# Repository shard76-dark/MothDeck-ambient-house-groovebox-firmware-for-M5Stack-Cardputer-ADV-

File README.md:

# MothDeck

MothDeck is ambient-house groovebox firmware for the [M5Stack Cardputer ADV](https://docs.m5stack.com/en/core/Cardputer-Adv) (Stamp-S3A, ESP32-S3): drums, a per-track FX insert, a four-track mixer, SD kits and loops, and BLE MIDI. It is a sibling of [MothOS](https://github.com/MothSynths): same song file, same BLE MIDI map, same voice and effect model, redrawn for the ADV's 240×135 colour screen and 56-key keyboard.

## Download the binary

**Use earphones or headphones.** Plug them into the 3.5 mm jack on the side of the Cardputer ADV. This firmware does not play through the internal speaker. The jack is how you hear the drums, the kits, and the loops. Unplugging the earphones does not switch the sound to the speaker.

**Latest Cardputer ADV image (flash this):** [`releases/mothdeck-cardputer-adv.bin`](releases/mothdeck-cardputer-adv.bin)

- Version 1.2.12
- SHA-256: `9b98e52296c0634d2577b3fa6f98c0125cec331b60e1f9f07e440d255c90aa24`
- Size: 1,235,872 bytes (app image, magic `E9`)
- 1.2.12 follows an external clock from the incoming ticks, keeps several MIDI channels sounding at once, and answers `status` with DTR and RTS low. Details are in [What 1.2.12 includes](#what-1212-includes). The air name is `Mothdeck`. Patterns are 1–8 bars and Play opens on a piano roll. Notes are in [`releases/CHANGELOG.md`](releases/CHANGELOG.md).
- Install notes: [`releases/INSTALL.md`](releases/INSTALL.md) — copy the `.bin` to a FAT32 card, install from [Launcher](https://github.com/bmorcelli/Launcher)
- Optional SD kits/loops: [`releases/mothdeck-sd-pack.zip`](releases/mothdeck-sd-pack.zip) · checksums: [`releases/SHA256SUMS`](releases/SHA256SUMS)

The public source and releases live in this repository. Flash the application image with [releases/INSTALL.md](releases/INSTALL.md). The same overview, with HTML meta tags for search and link previews, is [docs/index.html](docs/index.html).

## What 1.2.12 includes

1.2.12 is the Cardputer image to flash. It includes the 1.2.2 through 1.2.11 behavior. This image has not been tried on a Cardputer. Use earphones.

- **External sync.** Tempo is the incoming tick count over the timestamps. One beat follows a change. Two beats hold a steady tempo, so 80–138 land on that integer and a jump up to 180 shows within about two beats. The deck BPM is the fallback only when a gap is much longer than one tick. Copies of one tick count once. A run of sub-tick clocks does not race the playhead. Faster than 200 clamps to 200.
- **Live MIDI.** The event ring is 48 slots (was 256), the note-off tail is 16 (was 32), and clock groups are 32 (was 64). A note-on older than 40 ms is dropped. Note-offs stay. Clocks stay a counter.
- **Channels.** Channels 1, 5, 9, and 13 play track 1. Channels 2, 6, 10, and 14 play track 2. Channels 3, 7, 11, and 15 play track 3. Channels 4, 8, 12, and 16 play track 4. Channels 1–4 also select that track. Each track keeps its own four voices.
- **USB serial.** `status`, `help`, and `version` answer when the host leaves DTR and RTS low.
- **MothDiag 0.1.6.** Stats add `clock_hz`, the raw clock bytes per second. The clock line shows the musical rate and the raw rate. The image is [`releases/mothdiag-0.1.6.bin`](releases/mothdiag-0.1.6.bin).

## What 1.2.11 includes

1.2.11 is included in the 1.2.12 image. It includes the 1.2.2 through 1.2.10 behavior. This image has not been tried on a Cardputer. Use earphones.

- **Slot versions.** MothBoot 0.1.2 reads the version from the whole application image, so slot B shows the installed MothDeck version. MothBoot 0.1.2 is [`releases/mothboot-0.1.2.bin`](releases/mothboot-0.1.2.bin). Write it at `0x10000` from the ROM bootloader. A board already on 0.1.1 can keep that launcher for uploads.
- **USB serial.** `status`, `help`, and `version` answer on MothDeck's CDC port. Opening the port does not reboot the board into download mode.
- **Install from an app.** `diag.py --flash` sends `launcher` when an app is running, waits for MothBoot, and then copies the image. The port number can change on that reboot.
- **External sync.** A smoothed tempo locks to 180 from a full-rate clock or a thinned one. Duplicate clocks and a sub-tick burst do not race the playhead. The deck still needs to be near the source tempo for a thinned clock.
- **MothDiag 0.1.5.** Clocks are counted in the BLE callback, so a full-rate MPC does not fill the packet queue. MIDI BPM handles the 13-bit timestamp wrap and repeated timestamps. The image is [`releases/mothdiag-0.1.5.bin`](releases/mothdiag-0.1.5.bin).

## What 1.2.10 includes

1.2.10 is included in the 1.2.11 image. It includes the 1.2.2 through 1.2.9 behavior. Use earphones.

- **MothBoot.** Sending `launcher` restarts into MothBoot on the USB-Serial-JTAG port. MothBoot 0.1.1 is [`releases/mothboot-0.1.1.bin`](releases/mothboot-0.1.1.bin). A board still running MothBoot 0.1.0 needs a later factory image from the ROM bootloader before `--flash` can run at full speed.
- **Uploads.** `diag.py --flash` and `--sd-put` wait for an ack after each chunk and draw a progress bar.
- **MothDiag 0.1.4.** `status`, `help`, `stats`, and command replies are always sent. The image is [`releases/mothdiag-0.1.4.bin`](releases/mothdiag-0.1.4.bin).

## What 1.2.9 includes

1.2.9 is included in the 1.2.10 image. It includes the 1.2.2 through 1.2.8 behavior. This image has not been tried on a Cardputer. Use earphones.

- **Sync.** Settings has Internal, External, and Transport. External follows MIDI start, stop, and song position. Tempo comes from the BLE timestamps: a gap that covers several ticks of the current BPM is counted as those ticks. Set the deck near the MPC's tempo, then switch to External. Transport follows start, stop, and position and keeps the BPM you set. Internal keeps the deck clock.
- **MTC.** Quarter frames can start and stop the transport. When their spacing matches the rate in the message, the playhead seeks. A half-rate stream leaves the tempo on the deck, or on the scaled clock when MIDI clocks are arriving too.
- **MothDiag 0.1.3.** The diagnostic screen shows MIDI BPM, arrival BPM, the clock rate, and the MTC rate, and it redraws only the line that changed. Published as [`releases/mothdiag-0.1.3.bin`](releases/mothdiag-0.1.3.bin).

## What 1.2.8 includes

1.2.8 is included in the 1.2.9 image. It includes the 1.2.2 through 1.2.7 behavior. This image has not been tried on a Cardputer. Use earphones.

- **Clock.** An external clock follows the master from 40 to 200 BPM, including when several clocks share one BLE timestamp. The short-interval request stays pending until the link is 15 ms or faster, and it is asked again while the link is still slow. A catch-up of more than one step moves the playhead and sounds the step it lands on.
- **Notes.** A status byte after a clock is the note, unless another status follows it. A note-on that arrives while note-offs are waiting is queued behind them. A long run of clocks does not push the notes out of the packet.
- **USB MIDI.** The USB port is a MIDI device named Mothdeck and still a serial port. USB notes and clock use the same queue as BLE. Unplugging USB releases live notes. The MIDI page shows `USB MIDI` while a host has enumerated the port, and `USB off` otherwise.

## What 1.2.7 includes

1.2.7 is included in the 1.2.8 image. It has not been tried on a Cardputer on its own. Use earphones.

- **Gate.** With Rec on, a MIDI note-off stores how long the note was held. The length is 1 to 4 steps, in the same two bits a piano-roll hold already uses. The song file does not change. Rec off still only plays.
- **Quantize.** The note lands on the step that just played. Three or more of the six clocks in that step, or halfway through an internal step, move it to the next step. A late note at the end of the pattern wraps to step 0 of that same pattern, including while song mode is moving on to the next one.

## What 1.2.6 includes

1.2.6 is included in the 1.2.8 image. It has not been tried on a Cardputer on its own. Use earphones.

- **Clock counter.** MIDI clocks are counted instead of taking a queue slot each. A burst of ticks, including a 200 BPM run, still advances the pattern, and the notes in that packet stay behind the ticks that preceded them. Start, Continue, Stop, and Song Position stay in the queue in that order. Start clears ticks that have not been applied yet, and ticks that sit before Start in the same packet are not counted. Clocks between Song Position and Continue still count.
- **Quiet connect.** The production build does not print from the connect and interval callbacks. Pairing, the advertising packet, and the 7.5–15 ms request are unchanged. The dev build still prints those lines.

## What 1.2.5 includes

1.2.5 is included in the 1.2.8 image. It has not been tried on a Cardputer on its own. Use earphones.

- **Stop and disconnect.** MIDI Stop, and a Bluetooth link that drops, release live MIDI notes. The pattern, loops, and sampler keep going. CC 120 and CC 123 do the same for the channel that sent them.
- **Note-off.** A note-off releases the matching note and channel on whichever track sounded it, and it does not change the selected track. Controllers, then note-ons, give up queue slots first. A note-off or a transport message is kept while any of those can move.
- **Continue.** Continue stays on the current step. Clocks that arrived after a Song Position still count, so the step does not slip by a tick. An external clock still reads 40–200 BPM, and a faster clock clamps at 200.
- **Status.** The Settings page no longer prints a counter line. The MIDI page counts packets, messages, clocks, and notes. Fn+D on that page opens a status view with the shed counts, how long the MIDI drain took, and the step length of the safety release. Backspace closes it. A tonal note with no note-off releases after that many steps (192 by default, about 24 seconds at 120 BPM). Held arp is not timed.

## What 1.2.4 includes

1.2.4 is included in the 1.2.8 image. It has not been tried on a Cardputer on its own. Use earphones.

- **1.2.2.** NimBLE is reserved at boot, before the loop windows. Turning BLE on starts advertising and does not allocate, so it does not fail for lack of a free block. Unload BLE skips the stack on the next boot and frees that block for a large loop library. The toast says `BLE unloads after restart`.
- **1.2.3.** Incoming MIDI notes only play while Rec is off. They are not written into the pattern. Space turns Rec on, and then they record at the playhead. MIDI Start and Continue do not arm Rec. A piano-roll key while the transport is running follows that same rule.
- **1.2.4.** An external clock counts every `0xF8` in a BLE packet, including several that share one timestamp. Six clocks advance one 16th. The BPM on screen is smoothed over a beat and tracks from 40 to 200. A track sounds up to four notes at once. A fifth replaces the oldest. Note-off, including velocity 0, releases only the matching note and channel, so a stolen or retriggered note does not cut a different voice. Notes that arrive in one packet each get a voice. When the MIDI queue is nearly full, extra clocks are dropped so a chord behind them is kept.

## LilyGO TTGO T8

A separate port of MothDeck 1.2.4 runs on a LilyGO TTGO T8 V1.8 (ESP32-WROVER, 4MB flash, 4MB PSRAM, microSD). It lives on the [`ttgo-t8` branch](https://github.com/shard76-dark/MothDeck-ambient-house-groovebox-firmware-for-M5Stack-Cardputer-ADV-/tree/ttgo-t8) and is not merged into `main`. The Cardputer image in `releases/` is a different binary. Do not flash a TTGO image onto a Cardputer, or the Cardputer image onto a T8.

The pre-release is [ttgo-t8-v1.2.4](https://github.com/shard76-dark/MothDeck-ambient-house-groovebox-firmware-for-M5Stack-Cardputer-ADV-/releases/tag/ttgo-t8-v1.2.4). Wiring, the menu tree, and both images are in [docs/TTGO-T8.md](https://github.com/shard76-dark/MothDeck-ambient-house-groovebox-firmware-for-M5Stack-Cardputer-ADV-/blob/ttgo-t8/docs/TTGO-T8.md) on that branch.

- **PSRAM.** Loop windows, samples, the pattern grid, chord notes, and the tracker sit in PSRAM, so BLE and loops stay loaded together.
- **Chords.** A step holds up to four notes. The first stays in the song file, so an older song still loads. The other three are stored in PSRAM. With Rec on, MIDI notes that land in the same step stack. The piano roll draws each one as a block in that column.
- **4×4 keypad.** A membrane keypad mounted with the connector on top, so the top-left key is key 0. The menu is the original MothSynth function-key layout, extended so every MothDeck page is reachable from the 16 keys.
- **ST7789 and audio.** The stock image drives a confirmed ST7789 240×135. `ttgo-t8` plays through a PCM5102A over I2S. `ttgo-t8-dac` uses the ESP32's internal 8-bit DAC on GPIO25. Keypad R3 is GPIO25 on the PCM image and GPIO22 on the DAC image.

These TTGO images have not been flashed, and the keys have not been pressed on hardware.

## ESP32 DevKit handheld

A second target on this branch is a small handheld on a classic ESP32-WROOM-32 board, the 30-pin DOIT ESP32 DevKit V1 (ESP32-D0WD). Build it with `pio run -e esp32devkit_handheld`. The Cardputer envs are unchanged. The LilyGO T8 port stays on `ttgo-t8`; this carrier reuses that port's PCM5102A audio path and its 4×4 menu, and it does not merge the 1.2.4 tree.

The DevKit's own AMS1117 cannot run from one Li-ion cell (dropout is about 1.1 V). The carrier feeds 3.3 V into the DevKit 3V3 pin from an AP2112K-3.3 and leaves VIN open. Turn the slide switch off while flashing so the AP2112 and the DevKit regulator are not both on the 3.3 V rail.

### Pin table

Silkscreen on clone DevKits varies. Match the labels on the board you have. GPIO0, GPIO2, GPIO12, and GPIO15 are left open (strapping). GPIO6–11 are the flash bus and are not on the header. GPIO1 and GPIO3 stay on the USB UART. GPIO34, GPIO35, GPIO36, and GPIO39 are input-only, so the column pull-ups are on the carrier.

| Function | GPIO | Notes |
| --- | --- | --- |
| I2C SDA | 21 | SSD1306 0x3C and HT16K33 0x70, 4.7 kΩ to 3.3 V |
| I2C SCL | 22 | same bus |
| I2S BCLK | 26 | PCM5102A BCK |
| I2S WS | 25 | PCM5102A LCK |
| I2S DOUT | 27 | PCM5102A DIN |
| PCM5102A SCK | GND | PLL mode, not a GPIO |
| Keypad R1–R4 | 16, 17, 18, 19 | outputs, membrane order |
| Keypad C1–C4 | 34, 35, 36, 39 | inputs, 10 kΩ to 3.3 V |
| LED step | 4 | GPIO → 470 Ω → LED → GND |
| LED beat | 5 | same, active high |
| LED play | 13 | same |
| LED record | 14 | same. GPIO14 can twitch during boot |
| Battery sense | 33 | ADC1, 100 kΩ / 100 kΩ from the cell, 100 nF to GND |

### Keypad

Mount the membrane on the left of the case, rotated 90° clockwise, so the ribbon that sat at the bottom of an upright legend now leaves to the left. Straight wiring, membrane order R1 R2 R3 R4 C1 C2 C3 C4. The printed legend is sideways after the turn:

```
*  7  4  1
0  8  5  2
#  9  6  3
D  C  B  A
```

The firmware numbers keys in reading order on the upright device. Key 0 is the top-left key. `handheldPadKey(membraneRow, membraneCol) = membraneCol * 4 + (3 - membraneRow)`. The menu is the MothSynth 4×4 layout used on the T8: F1–F4 on the top row latch, then the next key runs that function. The note rows underneath are C at the bottom left. Holding F1 for about half a second arms BPM nudge (C −1, C# +1, D −5, D# +5).

### Power

Cell: a 603450 1200 mAh LiPo with a JST-PH 2.0 plug (about 6 × 34 × 50 mm). It fits the left bay under the keypad. An 18650 is cheaper per mAh and too thick for this case.

Charger: a TP4056 USB-C module that already includes the DW01 protection cell. The slide switch (SS-12D00 or similar) sits between the charger OUT+ and the AP2112 input. The AP2112K-3.3 (SOT-23-5, 600 mA) makes 3.3 V. EN is tied to VIN. 10 µF on the input, 10 µF on the output, 22 nF on BP.

Playing with BLE is budgeted at about 170 mA. Usable capacity is about 1200 × 0.85 mAh, so runtime is about six hours. Without the radio, about 110 mA and about nine hours.

### What is on the carrier

The board is 66 × 78 mm, two layers. Headers for the DevKit, the PCM5102A (jack toward the right edge), the SSD1306, the HT16K33 backpack, the keypad ribbon, and the TP4056. The four LEDs and the battery sense divider are on the board. Ground is a tracked mesh. KiCad 7's zone filler crashes in the environment this board was generated in, so there is no copper pour. Power tracks are 0.25 mm because a 0.5 mm track cannot pass between the 1.7 mm header pads.

The case is 154 × 96 × 22 mm. The membrane is on the left, the carrier on the right, the headphone socket on the right wall, USB-C and the DevKit USB socket on the bottom wall, and the 603450 in a tray under the keypad. Source is `hardware/mothdeck-handheld/case/mothdeck-handheld-case.scad`.

### BOM, approximate AUD

| Qty | Part | AUD |
| --- | --- | --- |
| 1 | ESP32 DevKit V1 30-pin | 9 |
| 1 | PCM5102A purple DAC board | 6 |
| 1 | SSD1306 128×64 I2C OLED | 6 |
| 1 | HT16K33 4-digit backpack | 8 |
| 1 | 4×4 membrane keypad | 3 |
| 1 | TP4056 USB-C module with protection | 3 |
| 1 | 603450 1200 mAh LiPo, JST-PH | 12 |
| 1 | AP2112K-3.3 | 0.50 |
| 1 | SS-12D00 slide switch | 0.80 |
| 4 | 3 mm LEDs | 0.40 |
| 1 | passives, headers, JST | 5 |
| 1 | PCB, five from JLCPCB, this board's share | 2 |
| 1 | PETG for the case | 2 |

About 58 AUD before shipping. Prices move; treat them as a shopping list, not a quote.

### Assembly

1. Confirm the DevKit silkscreen against the pin table before soldering the headers.
2. Solder the AP2112, the passives, and the LED resistors first. The LED anode is the resistor side, not the GPIO.
3. Add the headers. The PCM5102A SCK pin on the module is the one tied to ground on the carrier.
4. Flash with the slide switch off and USB plugged into the DevKit, not the charger.
5. Switch on from the battery only after 3.3 V measures about 3.3 V at the DevKit 3V3 pin.
6. The OLED and the 7-segment are wired to their headers and sit in the lid. While a pattern is running the 7-segment shows bar and beat. Stopped, it shows BPM.

### Trade-offs

- Both the 7-segment and the four LEDs fit.
- No microSD. Kits and loops that need the card are absent. The built-in drums and synths play.
- No USB MIDI. The DevKit USB port is a UART bridge. BLE MIDI is the transport. The image links with about 40 KB of DRAM left, and the BLE start check asks for a 36 KB contiguous block, so the radio can still refuse until a reboot frees enough. That is untested on hardware.
- The delay history is 2048 samples, about 46 ms, instead of the Cardputer's 8192.
- GPIO5 and GPIO14 can glitch high for a moment at boot. The beat and record LEDs may flash then.
- Ground is tracked, not poured, and the power tracks are 0.25 mm.

## Features

- Ambient house drums on the M5Stack Cardputer ADV: twelve distinct hits at the recorded pitch (kick, rim, snare, clap, hats, toms, shaker, ride, snap, crash)
- Groovebox session on the ESP32-S3: 4 tracks, patterns of 1–8 bars (16–128 steps of 16th notes)
- Per-track FX (filter, delay, reverb, bitcrush, drive, chorus, tremolo) and a mixer with volume, mute, and solo
- SD kits, plugin instruments, and loops. Loops stream from the card instead of filling RAM
- BLE MIDI peripheral (notes, clock, transport, bank, volume, pitch bend), named Mothdeck in the advertising packet, and a USB MIDI device on the same port as serial
- Built-in sounds are unsigned 8-bit mono at 22050 Hz so they fit the 8MB flash and the internal SRAM
- One-second amber moth splash, then the Play page, with a checked exit back to Launcher

This repository is the Cardputer ADV firmware. The PlatformIO target is `cardputer-adv`. `cardputer-adv-dev` is that same firmware with SD and speaker logs on USB serial. The board id in `platformio.ini` is `esp32-s3-devkitc-1` because PlatformIO has no Stamp-S3A entry; the pins in `include/BoardConfig.h` are the ADV. There is no second ADV build.

Everything it uses is on the board. There is no wiring. The headphone jack, display, keyboard, and microSD are brought up by M5Unified. The internal speaker does not play with this firmware; use earphones or headphones in the 3.5 mm jack. A card is optional. The built-in drums, sound effects, and tonal instruments are synthesized when the firmware is built. They are not recordings of anyone else's samples.

## Flash it

See [releases/INSTALL.md](releases/INSTALL.md) for the button sequence. Short version:

1. Copy `releases/mothdeck-cardputer-adv.bin` (the file that starts with `E9`) to a FAT32 card.
2. Boot [Launcher](https://github.com/bmorcelli/Launcher), press Enter on its splash, and install that file from the SD browser.
3. The next boot that follows the boot selection starts MothDeck.

`mothdeck-cardputer-adv-full.bin` is a USB flash of the whole chip. It replaces Launcher. Checksums for both images and for `mothdeck-sd-pack.zip` are in `releases/SHA256SUMS`.

Unzip `releases/mothdeck-sd-pack.zip` onto the card root when you want the extra kits, loops, and plugin instruments. You should end up with a `moth` folder at the top of the card. The built-in kit does not need the card.

## Boot

Power-on turns the backlight on, draws an amber moth on a grey panel for about one second, then draws the Play page. The splash does not wait for a key. Audio starts before the screen sprite. NimBLE is reserved then, before the loop windows, and the radio is not advertising. Rec is stopped. The card scan is last, and the loop windows use whatever is left. Space starts Rec. Turning BLE on only starts advertising. The codec is not started inside `M5.begin`, and GPIO42 is the codec data line, not an amplifier pin to drive high. Sound comes out of the 3.5 mm jack. The internal speaker stays quiet.

The moth is amber (`0xFD20`) on grey (`0x1082`). The splash marks that buffer as logical RGB565 before `pushImage`, so the moth stays amber instead of blue. The UI sprite is rgb332 (32,400 bytes) and is copied to the panel eight rows at a time. A full-frame 8-bit push grew a second DMA buffer and reset the ADV once the speaker was running. Loop windows are allocated only when a loop opens.

Hold Esc (the `` ` `` key) or the front button for about 0.7 seconds to leave for Launcher, including during that boot. Exit is offered only when the `APP_TEST` slot holds a real ESP32-S3 app image (header magic `E9`). Otherwise the menu entry is grey, the page says "Launcher not found", and the hold does not erase `otadata`. Details are in [releases/INSTALL.md](releases/INSTALL.md).

## What a session looks like

Tab moves between pages: Play, Instrument, FX, Mixer, Song, Loops, MIDI, Settings, and Exit when Launcher is present. `` ` `` on any page other than Play returns to Play. On Play, a tap of `` ` `` opens the page list. Space is play and stop, except while a menu is open.

There are 4 tracks. A pattern is 1 to 8 bars, and a bar is 4 beats of 4 sixteenth-notes, so 16 to 128 steps. A new song is 1 bar. The grid is still 256 steps, so four patterns fit up through 4 bars, three fit at 5 bars, and two fit at 6, 7, or 8 bars. Keys 5–8 select a pattern and stop at the last one that fits. Step timing matches MothOS: the mix is 44100 Hz, and one step is `11025 / beats-per-second` samples. Each track keeps its own instrument. Selecting another track recalls that track's instrument. It does not copy the previous one across.

The Play page is a piano roll: pitches down the left (C2 at the bottom through B5), time across, notes as blocks as wide as their hold. A one-bar pattern draws 8 pixels per step. Two bars use 6. Three bars and longer use 4, and the grid scrolls to keep the cursor on screen. While playback is running the cursor follows the playhead until you move it in time. Enter switches to the old 16-step strip, where Fn+`,` and Fn+`/` still page the bar (`B3/8`). Enter again returns to the roll. Settings has a Bars row; Fn+`,` and Fn+`/` on that row change the length without clearing notes. Song `N` still starts a new song, and it steps the length through 1–8 bars. A song saved with 16 steps loads as 1 bar. A song saved with 32 steps stays 2 bars. Other stored lengths round up to a whole bar, capped at 8. A one-step note is stored as before. A longer hold (2–4 steps) uses two spare bits in that same note byte.

Page-by-page notes and the rest of the shots are in [docs/USER-GUIDE.md](docs/USER-GUIDE.md).

Audio runs on its own task on core 1. The UI reads a snapshot. It does not write the tracker from the draw path. The speaker is fed 256-frame blocks while fewer than two blocks are queued.

## Drums, kits, and the other instruments

The twelve built-in instruments are Drums, SFX, Sine, Square, Saw, Tri, Organ, Pluck, Bell, Flute, Bass, and Pad. The row after Pad is Loops. Plugin folders from the card appear under those.

Drums are twelve different hits, one per pad, played at the recorded pitch. Changing octave plays the same piece again. It does not speed the sample up. The upper row and the lower row of the same key are the same pad.

| Key | Pad | What you hear |
| --- | --- | --- |
| C | Kick | Sub with a click |
| C# | Rim | Short stick |
| D | Snare | Noise snare |
| D# | Clap | Layered clap |
| E | Closed hat | Bright short noise |
| F | Open hat | Longer hat |
| F# | Low tom | Pitched tom |
| G | Tom | Higher tom |
| G# | Shaker | Soft noise |
| A | Ride | Long metallic noise |
| A# | Snap | Short transient |
| B | Crash | Soft cymbal |

On the Instrument page, `,` and `/` load the previous or next kit onto Drums. Fn+`,` and Fn+`/` do the same. The line under the list is the kit name. Index 0 is always the built-in Ambient House kit in flash. Further kits are folders under `/moth/drums`. If the card has none, the toast says "No SD kits". `R` rescans instruments, kits, and loops. Enter assigns the highlighted row to the selected track only.

SFX is twelve different one-shots (riser, downlifter, zap, sweep, impact, noise, blip, siren, reverse, drop, bubbles, whoosh), one per key. Those do follow the octave. Sine through Pad are synthesized per sample: sine is a sine, square is rounded, saw is a detuned lead, triangle is a triangle, organ is drawbar sines, pluck closes a filter and decays, bell is decaying FM, flute is a slow sine with breath, bass is a sub plus detuned saws, and pad attacks slowly, stays detuned, and holds.

## Mixer and FX

These are different pages.

FX is the insert on the selected track: filter (off, low pass, high pass), cutoff, resonance, delay, feedback, mix, reverb send, bitcrush, drive, chorus, and tremolo, then Scale, Root, Arp, Glide, Osc2, Blend, and Coarse. Fn+`;` and Fn+`.` move the row. Fn+`,`, Fn+`/`, and Enter change the value. The list shows seven rows and scrolls. Delay follows the BPM as 1/32, 1/16, or 1/8. Each track keeps its own insert. Inserts are saved only when one is in use, which makes the song file version 3. Scale, a held arp, Osc2, blend, coarse, or glide make version 4.

Scale is off, major, minor, harmonic minor, mixolydian, phrygian, or chromatic. Root is the pitch class, C through B. A note from the keyboard, the sequencer, or BLE snaps to the nearest scale tone, and a tie goes down. On a sample patch the file's `root=` is the MIDI note the recording is at; `scaleroot=` is the scale's pitch class when both are set.

Arp is off, pat 1, pat 2, or held. Pat 1 and pat 2 are the older built-in interval walks. Held keeps the MIDI notes that are down (up to eight) and steps to the next one each 16th note. The Cardputer keyboard is one note at a time and does not send note-off, so a held chord comes from BLE. The first note sounds immediately. Releasing the last note stops the track.

Glide is the time from the previous note to the new one, in steps of 10 ms, up to 500 ms on the device (a patch file may say up to 2000). The first note snaps. Osc2 is a second sine, square, saw, or triangle, mixed by Blend (0–100, steps of 10) and transposed by Coarse (−24..24 semitones). It runs on built-in tones and on short samples.

The Play-page keys A, F, K, and L still cycle the older 0–2 low pass, retrig, wobble, and echo on the selected track.

Mixer shows all four tracks as volume faders, with the instrument name on each and the selected track highlighted. Fn+`;` raises the selected track and Fn+`.` lowers it (0–8). Fn+`,` and Fn+`/` move between tracks. `1`–`4` jump to a track. `M` mutes the selected track and `S` solos it. Volume is stored in every song version.

## Loops

Two ways to use card audio, both reading the same `/moth/loops` libraries.

The Loops page lists libraries and entries. Enter launches the row onto the selected track. `A` auditions. `Q` cycles quantize: now, beat, or bar. `S` stops the loop on the track. `R` rescans. Fn+`,` and Fn+`/` change library.

The Loops instrument (the row after Pad, id 63) is assigned like any other instrument. Notes on that track start one of the audio loops, wrapping if there are fewer loops than keys, lined up with the current bar. Playback follows the project BPM, so a faster song advances the file faster.

A loop is not copied into the heap. Playback reads a short window from the card (1024 frames, double buffered, up to four streams, five hold slots). The window is allocated when the loop opens and freed when it closes. Launch can wait for the next beat or the next bar.

## Memory

The release Settings screen does not print a heap readout. The Radio row says `off`, `adv`, or `conn`. Kilobyte figures stay on the MIDI page (`heap` and `blk`) and in the dev build's serial log. The Stamp-S3A has no PSRAM. As of 1.2.2, NimBLE is initialised at boot, before the loop pool and before the card scan, whether or not it is advertising. On and off only start or stop advertising, so the stack's footprint does not change. Loop windows are whatever contiguous RAM is left beside that stack. Unload BLE skips the stack on the next boot so the windows can use that block; the toast says `BLE unloads after restart`. Load BLE takes effect on the following boot, and the toast says `BLE loads after restart`. Each pattern step in RAM is two bytes (note, octave, instrument). The song file on the card stays the unpacked 256-step layout. Pattern storage does not grow when BLE is left off.

A kit or plugin that does not fit leaves the previous one selected. The toast says `Kit unchanged` or `Sound unchanged`. A loop library that cannot open every file says `Loops: N of M ready`. Without PSRAM the caps are:

| What | Limit |
| --- | --- |
| Built-in patch | No heap. The numbers sit on the voice |
| Subtractive or FM cycle | 168 frames, 336 bytes |
| Plugin sample | 4096 frames (8192 bytes), 4 loaded at once |
| Drum kit | 8000 frames total, 1800 per pad, one kit cache |
| Loop windows | Preferred pool is 20480 bytes: 5 slots × 1024 frames × 2 buffers × 2 bytes. One slot is 4096 bytes. Unloaded while BLE is on |

A patch that only sets a built-in, a cycle, or a short sample does not count as a loop. Turning BLE on leaves those plugins loaded. The six example folders are `a-minor`, `held-arp`, `glide-bass`, `saw-pluck`, `body`, and `room-drive` under `sd-card-example/moth/instruments/`.

An allocation also leaves about 8KB of internal heap for the rest of the system. A corrupt manifest or WAV is reported on the page and skipped.

## Sample format

Built-in drums, built-in sound effects, the SD pack, and the default output of `tools/wav_to_instrument.py` and `tools/wav_to_loop.py` are unsigned 8-bit mono PCM at 22050 Hz. 128 is silence. That is about 22 KB/s. A 44.1 kHz stereo 16-bit file is about 176 KB/s. The mix stays 44100 Hz and stretches 22050 up to it. Prefer mono. A 16-bit WAV still loads, and stereo is folded to mono. `--raw` on the instrument converter writes little-endian int16 at the source rate.

Regenerate the flash tables with `python3 tools/gen_samples.py` and the card pack with `python3 tools/make_sd_pack.py`.

## Card layout

```
/moth/slot1.mos … slot4.mos
/moth/instruments/<folder>/manifest.txt
/moth/instruments/<folder>/sample.wav    (or sample.raw)
/moth/drums/<kit>/manifest.txt
/moth/drums/<kit>/*.wav
/moth/loops/<library>/manifest.txt
/moth/loops/<library>/*.wav              (or raw, or .pat)
```

The pack in `releases/mothdeck-sd-pack.zip` contains:

| Path | What it is |
| --- | --- |
| `moth/drums/808` | 808-style kit |
| `moth/drums/dusty` | Ambient kit, dulled |
| `moth/loops/house` | Four one-bar loops at 120 BPM (kick, hats, chord, sub), 44100 frames, about 44 KB each |
| `moth/instruments/ep` | Electric piano, one-shot |
| `moth/instruments/reese` | Detuned saw bass, looping |
| `moth/instruments/saw-lead` | Two detuned saws, looping |
| `moth/instruments/soft-pad` | Slow detuned sines, looping |
| `moth/instruments/house-pluck` | Short pluck, one-shot |
| `moth/instruments/air-bell` | FM bell, one-shot |
| `moth/instruments/a-minor` | Patch: built-in bass, A minor |
| `moth/instruments/held-arp` | Patch: built-in saw, held-note arp |
| `moth/instruments/glide-bass` | Patch: bass, second saw, 90 ms glide |
| `moth/instruments/saw-pluck` | Patch: subtractive saw and a low-pass |
| `moth/instruments/body` | Patch: short pluck sample |
| `moth/instruments/room-drive` | Patch: sine, drive, delay, reverb, chorus |

Kit pad order is kick, rim, snare, clap, hat, openhat, perc, tom, shaker, ride, snap, crash. `perc.wav` is the low tom. Each pad file is already inside the 1800-frame and 8000-frame cache. Plugin samples in the pack are 3600 frames at 22050 Hz, under the 4096-frame cap. A kit folder is `mothdeck-kit 1`, a `name=`, and exactly twelve `pad=` lines.

```bash
python3 tools/wav_to_instrument.py take.wav card/moth/instruments/take --name take --root 60
python3 tools/wav_to_loop.py --name house --bpm 120 --bars 1 --tags drums \
    card/moth/loops/house kick.wav hats.wav
```

Those two commands resample to 22050 Hz and write 8-bit mono WAV. Song, instrument, loop, kit, and pattern bytes are specified in [docs/FORMATS.md](docs/FORMATS.md).

Plugins get ids 12–62. Id 63 is Loops. A song stores the folder name. If that folder is missing at load, the track falls back to the drum bank. A song that stays on the built-in instruments is a 3155-byte MothOS version 1 file. Plugins and loops make version 2. An insert effect makes version 3. Scale, a held arp, a second oscillator, or glide makes version 4.

## Screenshots

Shots of the MothDeck UI, at 2×, sit next to Play, Instrument, FX, and Loops above, and next to MIDI and Settings in the keyboard sections below. The Play, Instrument, FX, Loops, MIDI, and Settings pictures are the 1.2.0 screen. The MIDI-mode notice is the 1.2.1 wording (`MIDI mode: loops off.` / `Save song? Y / N`). Native 240×135 files are beside the 2× files in [docs/screenshots/](docs/screenshots/). Each page's keys are written out in [docs/USER-GUIDE.md](docs/USER-GUIDE.md).

## Keyboard

The drawings follow `src/Ui.cpp` and the 4×14 matrix in M5Cardputer `Keyboard.h`. Regenerate them with `python3 tools/make_keymap.py`. Each key shows the unshifted action. A caption on the key is the Fn action where that differs.

Esc is the grave key. The arrow legends are `;` up, `,` left, `.` down, `/` right, and they only move something while Fn is held, except on the Instrument page where `,` and `/` load kits by themselves. On the piano roll those four move the cursor. On the 16-step strip, Fn+`,` and Fn+`/` page the bar. Fn+`-` and Fn+`=` change speaker volume by 12 on every page. Fn plus any other key still does that key's normal action.

Ctrl or Shift substitutes the key's shifted glyph before the UI lowercases it. Letter commands still match. Digit and punctuation commands do not: Ctrl+1–8 is `!@#$%^&*` and does not clear a track or pattern, and Shift+`,` is `<` rather than the high C. Ctrl+N still starts a new song.

| Keys | Action |
| --- | --- |
| Tab | Next page. Shift+Tab or Ctrl+Tab goes to the previous page. While the page list is open, Tab moves the highlight and leaves the list up |
| Space | Play / stop. While a menu is open, Space does nothing |
| `` ` `` tap | On Play, toggle the page list. On any other page, return to Play. While the page list, name editor, or Exit confirm is open, `` ` `` cancels that menu |
| `` ` `` or the front button, held ~0.7s | Exit to Launcher, including during boot |
| 1–4 | Select track. On Song, select a slot and report full or empty |
| 5–8 | Select pattern. On Song, these keys do nothing |
| 9 / 0 | On Instrument, previous / next instrument. Elsewhere, previous / next BPM slot |
| `-` / `=` | Nudge the current BPM slot by 1 (40–240). With Fn, speaker volume ±12 |
| Backspace | On Play, clear the step under the cursor. In the name editor, delete one character. On the page list or Exit confirm, cancel back to Play. On any other page, return to Play |
| Ctrl+N | New song at the current length, without advancing that length |

### Play

`Z X C V B N M ,` are C D E F G A B C for the current octave. Comma is the C above that octave. `S D G H J` are C# D# F# G# A#. `Q` through `]` is the next octave, chromatic. Shift adds an octave on letter notes, Alt adds another, Opt subtracts one. They stack and clamp to four octaves, MIDI C2–B5. On drums, both octaves of a key play the same pad at the recorded pitch.

| Key | Action |
| --- | --- |
| A | Low pass, cycles 0–2 |
| F | Retrig, cycles 0–2 |
| K | Wobble, cycles 0–2 |
| L | Echo, cycles 0–2 |
| `;` | On the roll, if the cursor is on a note, cycle that note's hold through 1–4 steps. On an empty cell, or on the 16-step strip, send note-length `L` with the stored length. It does not step. The voice stores 4 minus that value. Fn+`;` moves the roll cursor up a semitone, and moves the page list up when the list is open |
| `'` | Toggle sampler mode |
| `\` | Cycle the octave |
| `.` | Copy pattern. Fn+`.` moves the roll cursor down a semitone, and moves the page list down when the list is open |
| `/` | Paste pattern. Fn+`/` moves the roll cursor one step later. On the 16-step strip it pages to the next bar |
| Enter | Toggle the piano roll and the 16-step strip |

Played keys are also sent as BLE MIDI note-on on the selected track's channel.

While the page list is open it takes every key. Fn+`;` and Fn+`.` move the highlight, Tab does the same, Enter stays on the highlighted page, and `` ` `` or Backspace returns to Play. Notes, space, track, pattern, and BPM keys do nothing until the list closes.

### Instrument

`9` / `0` and Fn+`;` / Fn+`.` move the instrument list. Enter assigns the row to the selected track only. Folders under `/moth/instruments` are listed after the built-ins. A `mothdeck-patch 1` folder copies its voice, FX, scale, arp, and glide numbers onto that track. A `mothdeck-instrument 1` folder loads the sample or cycle as before. `R` rescans. `,` and `/` load drum kits, as described above. 1–4 still select the track and 5–8 the pattern. The four names across the top of the page are tracks 1–4.

### FX

Described above. `` ` `` or Backspace returns to Play.

### Mixer

Described above. `` ` `` or Backspace returns to Play.

### Song

| Key | Action |
| --- | --- |
| 1–4 | Select the slot |
| 5–8 | No action |
| S / L / X / T | Save, load, delete, slot status |
| N | Start a new song one bar longer, wrapping from 8 back to 1. From a 1-bar song the first press is 2 bars |
| C / V / G | Copy pattern, paste pattern, paste all patterns |
| M | Toggle song mode and pattern mode |
| H | Toggle master volume |
| B | Next BPM slot |
| Enter | Load the selected slot |

`9` and `0` still move the BPM slot. Ctrl+N starts a new song at the current length and does not advance it.

### Loops

Described above. Fn+`;` and Fn+`.` move through every entry in the library. The list scrolls. If the stream windows cannot hold every audio loop, the page says `Loops: N of M ready`. While BLE is on the page says `MIDI mode: loops off`, and Enter, `A`, and the Loops instrument do not open a stream.

### MIDI

The page shows the real radio state, the stored name, and the channel map. It says "MIDI advertising" only while the controller is advertising. At boot it says `BLE off`. If the stack cannot start, the status says `restart` or `BLE off`. While a host is connected, the status row also shows the negotiated connection interval (`link 15.0ms`). The channel-map line also shows `USB MIDI` while a computer has enumerated the port, and `USB off` otherwise. Under the map it counts packets, messages, clocks, and notes (`pk`, `msg`, `clk`, `note`). Fn+D opens a status view and Backspace closes it. A stored name longer than 8 characters is shortened in the advertising packet, and the page shows that shorter name in parentheses. `E` jumps to Settings and starts editing the BLE name. Enter does nothing here.

### Settings

Rows: speaker, brightness, BLE name, BLE, Unload BLE, battery, radio, card, bars. The radio row shows `off`, `adv`, or `conn`. The dev build uses that row for a heap readout instead. Fn+`;` and Fn+`.` move the row. Fn+`,` and Fn+`/` change speaker volume or brightness by 8 when that row is selected (brightness stays at least 10). On the BLE row the same keys turn the radio off and on. Off stops advertising, disconnects a host, ignores incoming MIDI, and loads loop windows again. On turns Rec off, unloads loops, and advertises. NimBLE is already resident from boot, in the same place 1.1.0 paired from, so On does not allocate and does not fail. Off stops advertising and loads the loop windows that fit beside the stack. The choice is stored and defaults to off. A 1.1.1 setting of on is not read, so the radio stays off until you turn it on. If the open project has a loop on a track, or a track on the Loops instrument, On shows `MIDI mode: loops off.` and `Save song? Y / N`. Y saves, N skips, and either one then loads an empty project. `` ` `` cancels and leaves BLE off.

The two Settings pictures are the 1.2.0 screen. The version line says `v1.2.0`, and the row under Battery says Free RAM. On 1.2.8 that row says Radio (`off`, `adv`, or `conn`) and the version line says `v1.2.8`. There is no counter line under the rows.

Unload BLE is separate. Enter on that row stores the choice and skips BLE on the next boot, which is when the loop windows can take that block. It does not tear the stack down in this session: NimBLE's deinit races the host task and releasing its memory blocks a later init, and either one can reset the board while the speaker is running. The row says `next boot` and the toast says `BLE unloads after restart`. After that boot the BLE row says `unloaded`. Enter on Load BLE stores the choice and the toast says `BLE loads after restart`. The next boot initialises NimBLE before the loop pool. Fn+`,` before the reboot cancels a pending unload.

On the Bars row Fn+`,` and Fn+`/` set the pattern length from 1 to 8 bars and leave the notes in place. Enter on the BLE name row starts typing. Enter again applies the name and restarts advertising when the radio is on. While the name editor is open it takes every key: glyphs are lowercased and appended, up to 16, Backspace deletes one character, and `` ` `` cancels. Space does not play and is not typed.

### Exit

The Exit page is a confirm, and it is in the page list only when a Launcher image is detected. Enter clears the OTA boot selection and restarts toward Launcher. `` ` `` or Backspace returns to Play. Notes, space, track, pattern, and BPM keys do nothing on this page.

## MIDI

On an MPC Live II, open Menu, then Preferences, then Bluetooth. Turn BLE on in Settings first. Pair Mothdeck, then Connect. Then open MIDI / Sync and enable Mothdeck on the MIDI input ports. Turn Sync receive on when the MPC should drive the pattern clock. If the MPC still has a bond for the old name `MothDeck`, forget that device and pair `Mothdeck`.

Advertised as a BLE MIDI peripheral on legacy connectable advertising. The name `Mothdeck` and the MIDI service UUID are both in the primary advertising packet, which is what an MPC lists. A name longer than 8 characters is shortened there; the full name is in the scan response and on the MIDI page. The stack is NimBLE, and its controller memory is internal RAM, reserved at boot before the loop windows. The Stamp-S3A has no PSRAM. Audio starts before the screen sprite. Advertising stays off until Settings turns it on, and that switch does not allocate. Unload BLE frees the stack's block on the next boot so a large loop library can use it. The sprite is rgb332 (32,400 bytes) and is expanded to the panel eight rows at a time, so the blit does not allocate a second full frame. Pairing is Just Works with bonding and no passkey, the same security 1.1.0 used. The host starts pairing. MIDI bytes are not gated on encryption, so a host that never finishes pairing can still connect.

Incoming BLE MIDI is parsed a whole packet at a time. One packet may hold several notes and interleaved `0xF8` clocks; Note On with velocity 0 is Note Off. Channels 1, 5, 9, and 13 play track 1. Channels 2, 6, 10, and 14 play track 2. Channels 3, 7, 11, and 15 play track 3. Channels 4, 8, 12, and 16 play track 4. Channels 1–4 also select that track. A higher channel leaves the selection alone. Each track keeps its own four voices. While Rec is off those notes only play, and they are not written into the pattern. Space arms Rec, and then they record on the step that just played. Three or more clocks into that step, or halfway through an internal step, round to the next step. The end of the pattern wraps to its own step 0. Note-off stores the hold as 1 to 4 steps in the existing length bits. MIDI Start, Continue, Stop, and Song Position move the transport and do not arm Rec. Clock is 24 per quarter note, and a pattern step is a 16th, so six clocks advance one step. Start puts the current pattern on bar 1 step 1 and plays that step. Continue resumes on the current step and keeps the clock phase, including clocks that arrived after Song Position. Song Position is a sixteenth-note index taken modulo the pattern length, and it does not switch patterns. The tempo shown on screen is the tick count over the timestamps. One beat follows a change and two beats hold a steady tempo, so 80–138 land on that integer. The deck BPM is the fallback only when a gap is much longer than one tick. An external clock clamps at 200. Several clocks that share one timestamp count separately when each slice is a real tick, and copies of one tick count once. A note-on older than 40 ms is dropped. Note-offs stay. Those clocks are a counter, not a slot each, so a burst does not push the notes out of the queue. Ticks before Start in the same packet are not counted. A track sounds up to four MIDI notes at once. A fifth replaces the oldest. Note-off, including velocity 0, releases only the matching note and channel, on the track that sounded it, and does not change the selected track. Notes in one packet each get a voice. When the queue is under pressure, controllers are dropped before note-ons. Note-offs and transport stay. Stop, and a link that drops, release live notes and leave the pattern, loops, and sampler running. A tonal note with no note-off releases after a long run of steps. Space still starts and stops the internal clock.

MIDI has no message for the other machine's sequence length. Auto-length watches for Start, or a Song Position of 0, after a whole number of bars of clocks (one bar is 96 clocks, and the count has to land within half a beat of that). It rounds to 1–8 bars and adopts that length. The MPC Live II manual documents MIDI Clock, Start, Stop, and Continue. It does not document a message at the sequence loop point, and in practice the Live II keeps the clock running through the loop and does not send Start or Song Position there. When nothing comes back to zero, auto-length leaves the length set on the device. Phase still follows the clock from the last Start: a 1-bar pattern stays locked to a longer MPC sequence, and a length that does not divide the MPC sequence drifts until the next Start or Song Position. Stop, Space, and a Song Position that is not zero throw away the measurement so the next Start does not resize from a partial pass.

After a connection has been up for 250 ms the link asks for a 7.5–15 ms interval. The production build does not print that exchange. The dev build does, and the MIDI page shows it as `link 15.0ms` (or whatever was negotiated). The characteristic accepts write and write-without-response. While connected, the audio task drains MIDI every 32 samples and renders 128-sample blocks with one buffer queued, instead of waiting out two 256-sample blocks. The MIDI page counts packets, messages, clocks, and notes. Fn+D on that page opens status: shed clocks, note-ons, and note-offs, a full ring, parser misses, safety releases, late speaker refills, play retries, the longest MIDI drain, free RAM, and the safety step length. The screen redraws when that picture changes. Settings does not print a counter line. Its Radio row says whether BLE is off, advertising, or connected. Change the BLE name on Settings. The name is stored in NVS. The first boot of 1.1.2 stores `Mothdeck`. Packets are Apple-style timestamped MIDI, the same codec as MothOS.

| Message | Map |
| --- | --- |
| Note on/off | Channels 1, 5, 9, 13 are track 1; 2, 6, 10, 14 are track 2; 3, 7, 11, 15 are track 3; 4, 8, 12, 16 are track 4. Channels 1–4 also select the track. Notes 36–83 are C2–B5. Stored only while Rec is on. Note-off finds the track that sounded the note |
| CC 120 / CC 123 | Release live notes on that channel. The pattern, loops, and sampler stay |
| CC 0 / CC 32 bank | Instrument. MSB 0–11 built-in, 12–62 plugin id, 63 Loops. A non-zero LSB still spreads the 14-bit value across the 12 built-ins, as MothOS does |
| CC 1 mod | Low pass |
| CC 7 / CC 39 volume | 14-bit, mapped to voice volume 0–8 |
| Pitch bend | Per channel, ± the voice pitch ratio |
| Clock `0xF8` | 24 per quarter. Six clocks advance one 16th. Clocks are a counter. Ticks before Start in that packet are not counted. Tempo is ticks over timestamps, one beat while it is moving and two beats while it is steady, and clamps at 200 |
| Start `0xFA` | External sync, current pattern, bar 1 step 1. Does not arm Rec. Learns a loop length only after a full run of clocks |
| Continue `0xFB` | Resume external sync on the current step, keeping the clock phase. Does not arm Rec |
| Stop `0xFC` | Stop, leave external sync, cancel auto-length, release live notes |
| Song position `0xF2` | Sixteenth index modulo the pattern length. Zero can learn the loop; any other value cancels the measurement |

Keypad notes are sent back out as note-on on the track channel. Bank and volume are sent when the matching control changes.

## Build

PlatformIO, pioarduino 55.03.312-1 (Arduino-ESP32 3.3.12). Libraries are pinned: M5Unified 0.2.25, M5GFX 0.2.32, M5Cardputer 1.1.1.

```bash
pip install platformio
./build.sh
```

`pio run -e cardputer-adv-dev` builds the same firmware with SD, speaker, heap, and MIDI-counter logs, plus Arduino error logs, on the USB serial port. The release image prints the version at boot, a line when advertising starts, and a line when audio or BLE init fails. Packet, clock, and note counts stay on the MIDI page in both builds. Shed counts stay on the hidden status view.

`build.sh` regenerates the built-in waveforms, the example card tree, runs the host tests, and writes:

- `releases/mothdeck-cardputer-adv.bin` — install this from Launcher
- `releases/mothdeck-cardputer-adv-full.bin` — USB flash only; it replaces Launcher
- `releases/SHA256SUMS`

Host tests alone:

```bash
bash tools/run_tests.sh
```

The image is built `qio_qspi` at 80 MHz. That is the memory type on the Arduino-ESP32 `m5stack_cardputer` board (QIO flash, QSPI PSRAM type, PSRAM left disabled) and on Launcher's Cardputer environment. `-DBOARD_HAS_PSRAM` is not set, so M5GFX does not prefer a PSRAM heap that is not there. `qio_opi` would boot-init octal PSRAM on GPIO33–37, which this board uses for the display.

`partitions/cardputer_adv_8MB.csv` is the development table used by a USB flash and by the linker. Launcher does not use it. Launcher installs the application image into an OTA slot after its own `APP_TEST` image.

## Hardware

Cardputer ADV: Stamp-S3A (ESP32-S3FN8, 8MB flash, no onboard PSRAM), ST7789 240×135, TCA8418 keyboard at I2C `0x34` (SDA 8, SCL 9), ES8311 on the same I2C bus at `0x18`. GPIO42 is the codec data line (DSDIN), GPIO41 is bit clock, GPIO43 is word select, and GPIO46 is the codec microphone data. The NS4150B speaker amp follows the codec, and its enable pin is not a GPIO: the board pulls it on, and the 3.5 mm jack turns it off while a plug is inserted. This firmware still does not play through that speaker. Use earphones or headphones. microSD is a separate SPI bus (SCK 40, MISO 39, MOSI 14, CS 12) with GPIO5 held high before mount. Display pins are MOSI 35, SCLK 36, CS 37, DC 34, RST 33, backlight GPIO38. Battery ADC is GPIO10. The front button is GPIO0. Grove (GPIO1 / GPIO2) is left unused. The IMU is left off.

Octal PSRAM uses GPIO33–37. Those pins are the display, so a PSRAM module cannot be added to this Stamp-S3A, and the firmware stays on `qio_qspi`. Both hardware SPI controllers are already in use, one for the display and one for the microSD. A Grove SPI RAM board is not a supported upgrade. Extra sample room is the microSD: kits and short plugin samples stay in a small RAM cache, and loops are read from the card while they play.

The splash art is `docs/splash-moth.png`. Regenerate the embedded mask with `python3 tools/make_splash.py`.

## Site

GitHub Pages publishes the `docs/` folder on `main`. After that setting is on, the site is:

https://shard76-dark.github.io/MothDeck-ambient-house-groovebox-firmware-for-M5Stack-Cardputer-ADV-/

`docs/robots.txt` allows indexing and names `sitemap.xml`. `docs/sitemap.xml` lists that Pages URL. `docs/index.html` carries the description, Open Graph, Twitter card, and JSON-LD (`SoftwareApplication` and `WebSite`).

## Project layout

```
include/     headers, including the codecs the host tests compile
src/         firmware
test/        host tests (MIDI, song v1/v2/v3, per-track FX, manifests, WAV, synth render)
tools/       sample generator, WAV converters, keymap and splash tools, test runner
docs/        project site (index, robots, sitemap), user guide, screenshots, file formats, keymap drawings, splash art
sd-card-example/
partitions/  development table, not used by Launcher
releases/    application image, full-flash image, SD pack, checksums, install notes
```

## Licence

MIT. Copyright (c) 2024 MothSynths. See [LICENSE](LICENSE).

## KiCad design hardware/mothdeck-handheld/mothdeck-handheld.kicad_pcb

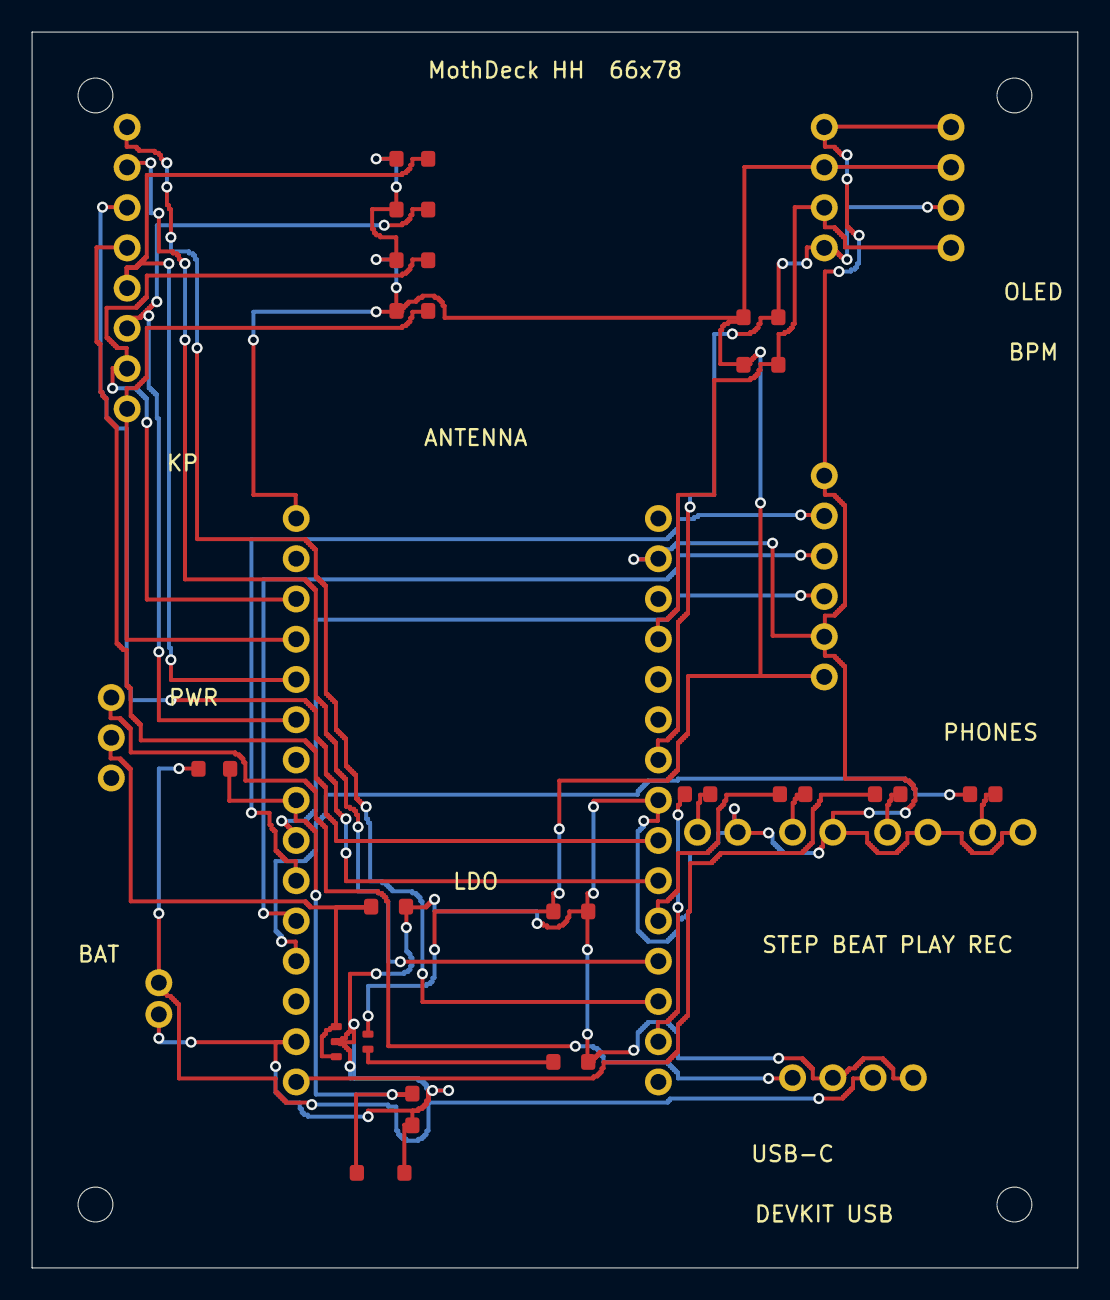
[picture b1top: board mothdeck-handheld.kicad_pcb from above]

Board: 2 copper layers, 66.0 x 78.0 mm, 34 parts (0 on the bottom side), 28 nets.

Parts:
C1: 10u; C1
C2: 10u; C2
C3: 22n; C3
C4: 100n; C4
D1: LED; D1
D2: LED; D2
D3: LED; D3
D4: LED; D4
H1: M2; H1
H2: M2; H2
H3: M2; H3
H4: M2; H4
J1: KEYPAD; J1
J2: BAT; J2
J3: DevKit_L; J3
J4: DevKit_R; J4
J5: OLED; J5
J6: 7SEG; J6
J7: PCM5102; J7
J8: TP4056; J8
R1: 100k; R1
R2: 100k; R2
R3: 4k7; R3
R4: 4k7; R4
R5: 10k; R5
R6: 10k; R6
R7: 10k; R7
R8: 10k; R8
R9: 470; R9
R10: 470; R10
R11: 470; R11
R12: 470; R12
SW1: PWR; SW1
U1: AP2112K-3.3; U1

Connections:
+3V3: C2.1, J3.1, J5.2, J6.2, J7.6, R3.1, R4.1, R5.1, R6.1, R7.1, R8.1, U1.5
ADC: C4.1, J3.8, R1.2, R2.1
BAT+: J2.1, J8.3, R1.1
BP: C3.1, U1.4
GND: C1.2, C2.2, C3.2, C4.2, D1.2, D2.2, D3.2, D4.2, J2.2, J3.14, J4.2, J4.8, J5.1, J6.1, J7.1, J7.5, J8.2, J8.4, R2.2, U1.2
I2C_SCL: J4.4, J5.3, J6.4, R4.2
I2C_SDA: J4.7, J5.4, J6.3, R3.2
I2S_BCK: J3.10, J7.2
I2S_DIN: J3.11, J7.3
I2S_WS: J3.9, J7.4
KP_C0: J1.5, J3.5, R5.2
KP_C1: J1.6, J3.6, R6.2
KP_C2: J1.7, J3.3, R7.2
KP_C3: J1.8, J3.4, R8.2
KP_R0: J1.1, J4.13
KP_R1: J1.2, J4.12
KP_R2: J1.3, J4.10
KP_R3: J1.4, J4.9
LED1_A: D1.1, R9.2
LED2_A: D2.1, R10.2
LED3_A: D3.1, R11.2
LED4_A: D4.1, R12.2
LED_BEAT: J4.11, R10.1
LED_PLAY: J3.15, R11.1
LED_REC: J3.12, R12.1
LED_STEP: J4.14, R9.1
VBAT: J8.1, SW1.1
VSW: C1.1, SW1.2, U1.1, U1.3

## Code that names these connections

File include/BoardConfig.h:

#ifndef BoardConfig_h
#define BoardConfig_h

// Two boards. The Cardputer ADV build leaves MOTHDECK_BOARD_HANDHELD at 0.
// The esp32devkit_handheld env sets it. Pins for that board are the DOIT
// ESP32 DevKit V1 (30-pin, ESP32-D0WD). Wiring is in the README.

#ifndef MOTHDECK_BOARD_HANDHELD
#define MOTHDECK_BOARD_HANDHELD 0
#endif

#define MOTHDECK_VERSION "1.2.12"
#define MOTHDECK_BLE_NAME_DEFAULT "Mothdeck"

// 1 compiles serial-monitor logs for the SD card and the speaker.
// 0 omits those Serial statements. Override with -DMOTHOS_DEV_LOG=1.
#ifndef MOTHOS_DEV_LOG
#define MOTHOS_DEV_LOG 0
#endif

#if MOTHDECK_BOARD_HANDHELD

#define BOARD_NAME "ESP32 DevKit"

// Classic ESP32-WROOM-32. No PSRAM, no microSD on this carrier, no USB MIDI
// (the DevKit USB port is a UART bridge). BLE MIDI is the radio transport.
// Strapping pins GPIO0, GPIO2, GPIO12, and GPIO15 are left open. Flash pins
// GPIO6-11 are not on the header. Input-only GPIO34-39 are the keypad
// columns and need external pull-ups. GPIO33 is ADC1 so the battery divider
// can be read while the radio is up.

#ifndef PIN_SD_SCK
#define PIN_SD_SCK -1
#endif
#ifndef PIN_SD_MISO
#define PIN_SD_MISO -1
#endif
#ifndef PIN_SD_MOSI
#define PIN_SD_MOSI -1
#endif
#ifndef PIN_SD_CS
#define PIN_SD_CS -1
#endif
#ifndef PIN_SD_AUX
#define PIN_SD_AUX -1
#endif

// PCM5102A I2S Philips. The module SCK pin is tied to GND on the carrier
// so the DAC uses its PLL. Do not drive SCK from a GPIO.
#ifndef PIN_I2S_BCLK
#define PIN_I2S_BCLK 26
#endif
#ifndef PIN_I2S_WS
#define PIN_I2S_WS 25
#endif
#ifndef PIN_I2S_DOUT
#define PIN_I2S_DOUT 27
#endif
#ifndef PIN_I2S_DIN
#define PIN_I2S_DIN -1
#endif

// Shared I2C bus: SSD1306 at 0x3C and HT16K33 at 0x70.
#ifndef PIN_I2C_SDA
#define PIN_I2C_SDA 21
#endif
#ifndef PIN_I2C_SCL
#define PIN_I2C_SCL 22
#endif
#ifndef MOTHDECK_OLED_ADDR
#define MOTHDECK_OLED_ADDR 0x3C
#endif
#ifndef MOTHDECK_HT16K33_ADDR
#define MOTHDECK_HT16K33_ADDR 0x70
#endif

// 4x4 membrane in membrane order (R1..R4, C1..C4). The clockwise remap is
// in KeypadMap.h. Columns are input-only; the board has 10k pull-ups.
#ifndef PIN_MX_R0
#define PIN_MX_R0 16
#endif
#ifndef PIN_MX_R1
#define PIN_MX_R1 17
#endif
#ifndef PIN_MX_R2
#define PIN_MX_R2 18
#endif
#ifndef PIN_MX_R3
#define PIN_MX_R3 19
#endif
#ifndef PIN_MX_C0
#define PIN_MX_C0 34
#endif
#ifndef PIN_MX_C1
#define PIN_MX_C1 35
#endif
#ifndef PIN_MX_C2
#define PIN_MX_C2 36
#endif
#ifndef PIN_MX_C3
#define PIN_MX_C3 39
#endif

// Active high. GPIO -> 470 ohm -> LED -> GND.
#ifndef PIN_LED_STEP
#define PIN_LED_STEP 4
#endif
#ifndef PIN_LED_BEAT
#define PIN_LED_BEAT 5
#endif
#ifndef PIN_LED_PLAY
#define PIN_LED_PLAY 13
#endif
#ifndef PIN_LED_REC
#define PIN_LED_REC 14
#endif

// Battery divider midpoint. 100k / 100k from the cell, so the pin sees half.
#ifndef PIN_BATT_ADC
#define PIN_BATT_ADC 33
#endif
#ifndef PIN_BTN_A
#define PIN_BTN_A -1
#endif

#else

// M5Stack Cardputer ADV (Stamp-S3A / ESP32-S3FN8, 8MB flash, no PSRAM,
// ST7789 240x135). Sample caches use PSRAM only when psramFound() is true.
// Everything used here is on the board: no external wiring.
// Display, keyboard (TCA8418), and the ES8311 codec are brought up by
// M5Unified / M5Cardputer. These pins are the ones the firmware touches
// directly (the SD bus and the I2S lines into the ES8311).

#define BOARD_NAME "Cardputer ADV"

// microSD on its own SPI bus. GPIO5 is held high before mount; Launcher
// does the same on the ADV because that pin otherwise fights the card.
#define PIN_SD_SCK 40
#define PIN_SD_MISO 39
#define PIN_SD_MOSI 14
#define PIN_SD_CS 12
#define PIN_SD_AUX 5

// ES8311 I2S, from the ADV schematic. M5.Speaker owns these after begin().
// GPIO42 is DSDIN (data into the codec). It is not an amplifier enable:
// driving it high as a plain GPIO replaces the I2S stream and mutes the
// speaker. The NS4150B follows the codec headphone driver, which is
// powered by the ES8311 register write in audioStart(). GPIO46 is ASDOUT
// (microphone data out of the codec).
#define PIN_I2S_BCLK 41
#define PIN_I2S_WS 43
#define PIN_I2S_DOUT 42
#define PIN_I2S_DIN 46

// Internal I2C: TCA8418 keyboard 0x34, ES8311 codec 0x18, BMI270 0x68.
#define PIN_I2C_SDA 8
#define PIN_I2C_SCL 9

// Front button, active low. Also sampled at boot for Exit to Launcher.
#define PIN_BTN_A 0

// Battery divider. M5.Power reads it once the board profile is detected.
#define PIN_BATT_ADC 10

// Grove HY2.0-4P. Not used by the firmware; listed so the port stays free.
#define PIN_GROVE_SDA 2
#define PIN_GROVE_SCL 1

#endif

// Audio rate. Step timing uses rate/4, matching MothOS (16th-note steps).
static const int kSampleRate = 44100;

// Built-ins are 0..11. 63 is the Loops instrument (notes play SD loops in
// time with the project BPM). Plugin folders use 12..62.
static const int kLoopsVoice = 63;

#endif
